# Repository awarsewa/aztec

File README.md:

# aztec
Bringing a 1976 pinball machine back to life.

[:corn: Wiki](https://github.com/awarsewa/aztec/wiki)

### The machine
Aztec is a Williams® pinball machine for 4 players. Check it out on the [Internet Pinball Machine Database](https://www.ipdb.org/machine.cgi?gid=119). There is also a [solid state version](https://www.ipdb.org/machine.cgi?gid=4828) of the same machine. Mine is from the electromechanical series -- and this is where the fun starts. Of course it wasn't functional. The entire cabinet had been completely gutted, with only a few tilt mechanisms left dangling about. However, the playfield and the backbox were still mostly intact. Repairing it seemed tough, but since it's cool to have your own pinball machine, I decided to give it a shot.

### The project
It would have been rather expensive and difficult to get original spare parts for, or replicas of, all the missing components. So why not replace aztec's brain with a microcontroller? The looks and feel of the machine would still be the same. Only what's under the hood would be slightly more modern. Maybe this is a sacrilege for real pinball lovers... I have a feeling it is. Like an inverse Frankenstein - pretty on the outside. But I already did it, so there's no way back and no repentance. If you want to know how I've done it, check out the [:corn: repository wiki](https://github.com/awarsewa/aztec/wiki).

### What's in this repository?
The source code running on the microcontroller and the PCB schematics. Basically everything you need to do something similar. 

### Getting involved
In case you have questions or suggestions, need support or simply want to get in touch, feel free to [send me a message](mailto:alexander.warsewa@posteo.net?subject=[Aztec]).

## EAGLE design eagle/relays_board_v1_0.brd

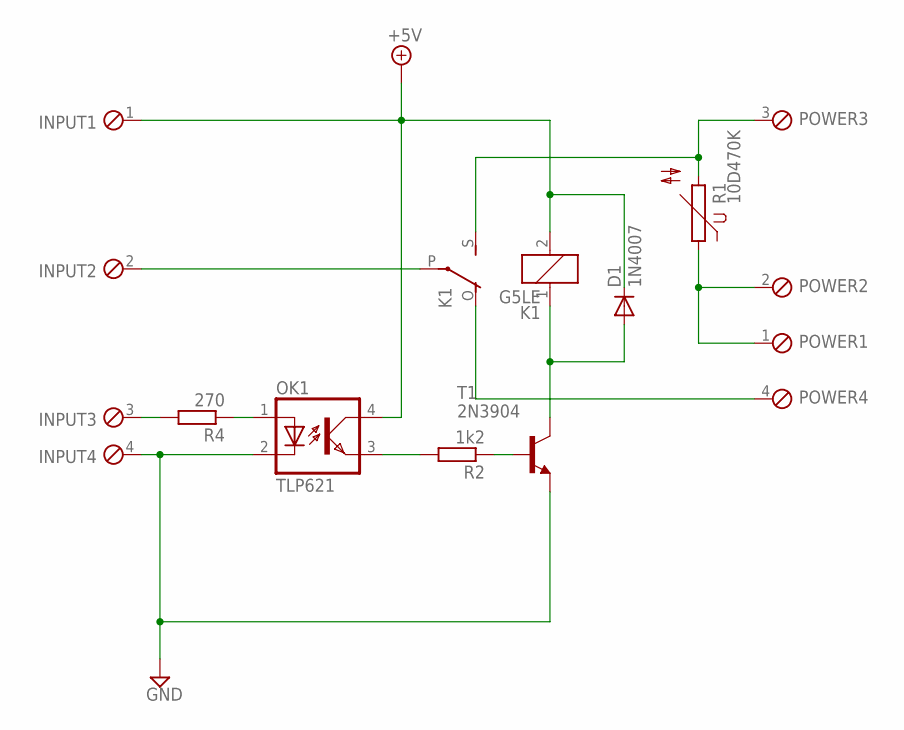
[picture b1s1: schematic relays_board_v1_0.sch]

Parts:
D1: 1N4007; DO41-10
INPUT: OSTTA040161; 040161
K1: G5LE
OK1: TLP621; DIL04
POWER: OSTTA040161; 040161
R1: 10D470K
R2: 1k2; 0204/7
R4: 270; 0204/7
T1: 2N3904; TO92

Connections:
+5V: D1.C, INPUT.1, K1.2, OK1.4 (COL)
GND: INPUT.4, OK1.2 (C), T1.3 (E)
unnamed: K1.O, POWER.4
unnamed: K1.S, POWER.3, R1.2
unnamed: POWER.1, POWER.2, R1.1
unnamed: INPUT.2, K1.P
unnamed: D1.A, K1.1, T1.1 (C)
unnamed: INPUT.3, R4.2
unnamed: OK1.1 (A), R4.1
unnamed: R2.1, T1.2 (B)
unnamed: OK1.3 (EMIT), R2.2

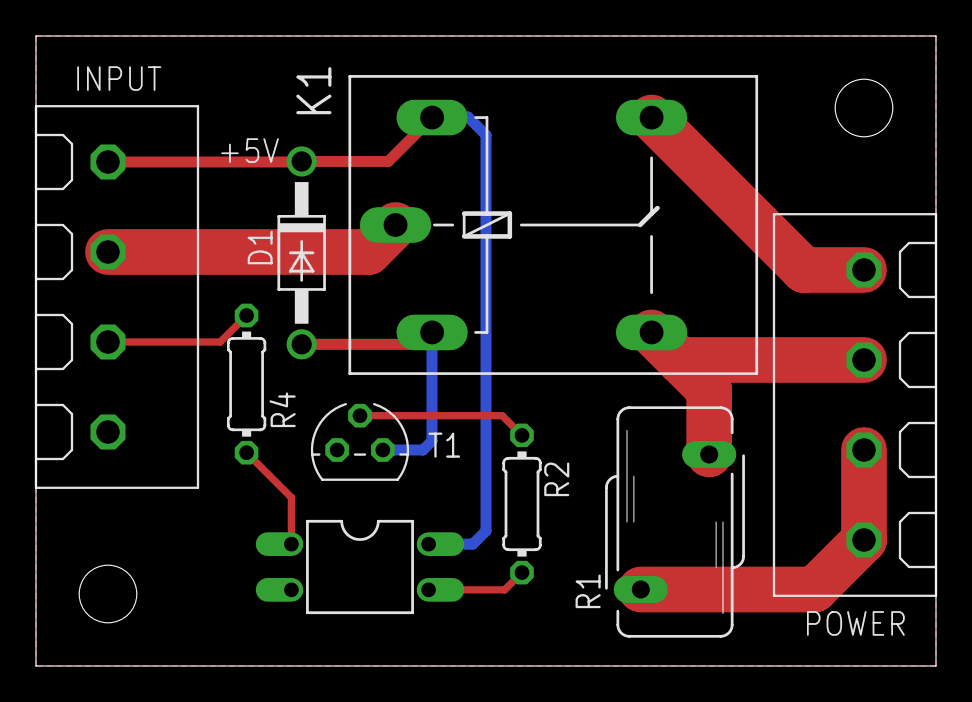
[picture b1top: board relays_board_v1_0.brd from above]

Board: 2 copper layers, 50.0 x 35.0 mm, 9 parts (0 on the bottom side), 11 nets.

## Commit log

2021-01-26 added source code
2021-01-26 added brains schematic
2021-01-26 added relays board
2021-01-27 Set theme jekyll-theme-cayman
2021-01-27 Set theme jekyll-theme-hacker
2021-02-04 cleaned up source code; removed recursion-free routines
2021-02-04 deleted pages website
2021-02-05 image for wiki
2021-02-05 added pcb rendering
2021-02-05 annotated PCB rendering
2021-02-06 added image of schematic symbols
2021-02-07 added image of Z relay
2021-02-10 added picture of ball count unit
2021-02-10 added score motor image
2021-02-12 added images of relay board
2021-02-12 changed image of relay pcb schematic
2021-02-12 added picture of power supply
2021-02-13 added image of my machine
2021-02-13 exchanged Eagle PCB with KiCAD version
2021-02-13 deleted old PCB versions
2021-02-13 igonre .ipynb*
